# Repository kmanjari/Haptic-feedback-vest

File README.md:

# Haptic Feedback Vest for Obstacle Detection

Visit our instructable at http://www.instructables.com/id/Haptic-Feedback-Vest-for-Obstacle-Detection/ to view a description of the system breakdown!

This design utilizes a stereo camera and software (Python and SimpleCV) that parses the user's surroundings into a depth map using a Raspberry Pi platform. This depth map is then used to vibrate the vest at a particular location to signify an obstacle in that location. For example, a vibration in the upper left region of the vest would indicate a hazard in the upper-body/leftward side of the surroundings. We also developed a PCB and integrated the physical piezoelectric hardware into a vest to create a functional and wearable prototype.

Final project for EE285: Embedded Systems Workshop course at Stanford University.

Contributors: Shalini Ranmuthu, Vikram Prasad, Jacqueline Speiser, Steven Lin, Meredith Burkle

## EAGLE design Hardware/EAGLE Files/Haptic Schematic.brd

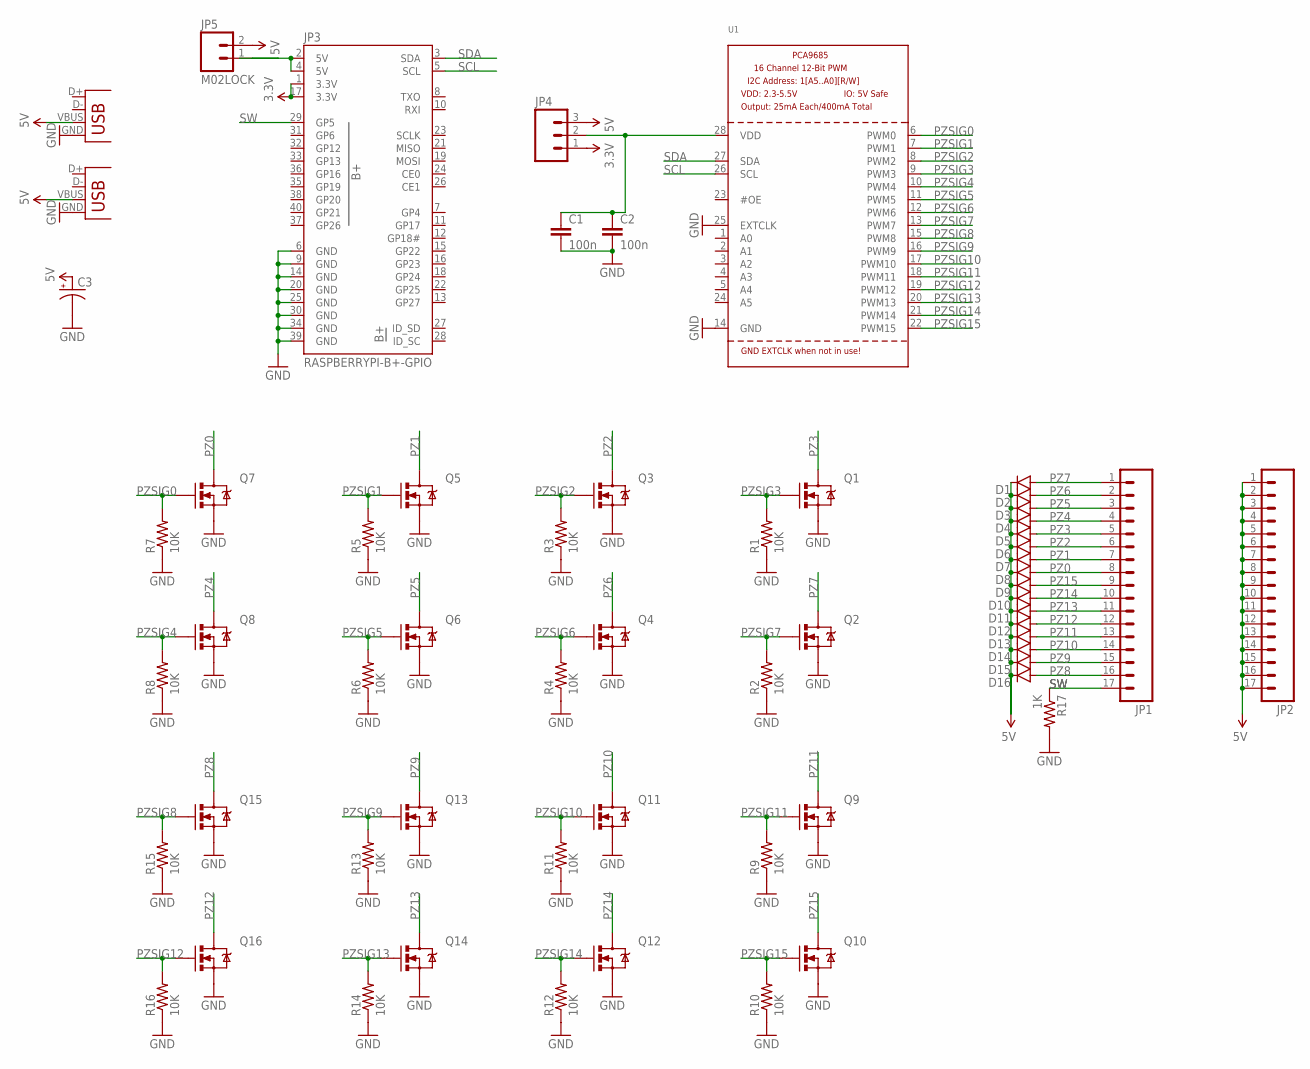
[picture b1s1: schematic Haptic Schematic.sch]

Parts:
C1, C2: 100n; 0805
C3: CAP_POLPTH2; CPOL-RADIAL-10UF-25V
D1, D2, D3, D4, D5, D6, D7, D8, D9, D10, D11, D12, D13, D14, D15, D16: DIODESOD523; SOD523
JP1, JP2: M17; 1X17
JP3: RASPBERRYPI-B+-GPIO; 2X20-SHROUDED
JP4: M03LOCK; 1X03_LOCK
JP5: M02LOCK; 1X02_LOCK
JP6, JP7: USB-B; USB-B-PTH
Q1, Q2, Q3, Q4, Q5, Q6, Q7, Q8, Q9, Q10, Q11, Q12, Q13, Q14, Q15, Q16: MOSFET-NCHANNEL2N7002PW; SOT323
R1, R2, R3, R4, R5, R6, R7, R8, R9, R10, R11, R12, R13, R14, R15, R16: 10K; 0805
R17: 1K; 0805
U1: PCA9685; TSSOP28

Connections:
3.3V: JP3.1 (3.3V), JP3.17 (3.3V), JP4.1
5V: C3.1 (+), D1.C, D2.C, D3.C, D4.C, D5.C, D6.C, D7.C, D8.C, D9.C, D10.C, D11.C, D12.C, D13.C, D14.C, D15.C, D16.C, JP2.1, JP2.2, JP2.3, JP2.4, JP2.5, JP2.6, JP2.7, JP2.8, JP2.9, JP2.10, JP2.11, JP2.12, JP2.13, JP2.14, JP2.15, JP2.16, JP2.17, JP4.3, JP5.2, JP6.VBUS, JP7.VBUS
GND: C1.2, C2.2, C3.2 (-), JP3.6 (GND), JP3.9 (GND), JP3.14 (GND), JP3.20 (GND), JP3.25 (GND), JP3.30 (GND), JP3.34 (GND), JP3.39 (GND), JP6.GND, JP7.GND, Q1.2 (S), Q2.2 (S), Q3.2 (S), Q4.2 (S), Q5.2 (S), Q6.2 (S), Q7.2 (S), Q8.2 (S), Q9.2 (S), Q10.2 (S), Q11.2 (S), Q12.2 (S), Q13.2 (S), Q14.2 (S), Q15.2 (S), Q16.2 (S), R1.1, R2.1, R3.1, R4.1, R5.1, R6.1, R7.1, R8.1, R9.1, R10.1, R11.1, R12.1, R13.1, R14.1, R15.1, R16.1, R17.2, U1.14 (GND), U1.25 (EXTCLK)
unnamed: JP3.2 (5V), JP3.4 (5V), JP5.1
unnamed: C1.1, C2.1, JP4.2, U1.28 (VDD)
PZ0: D8.A, JP1.8, Q7.3 (D)
PZ1: D7.A, JP1.7, Q5.3 (D)
PZ2: D6.A, JP1.6, Q3.3 (D)
PZ3: D5.A, JP1.5, Q1.3 (D)
PZ4: D4.A, JP1.4, Q8.3 (D)
PZ5: D3.A, JP1.3, Q6.3 (D)
PZ6: D2.A, JP1.2, Q4.3 (D)
PZ7: D1.A, JP1.1, Q2.3 (D)
PZ8: D16.A, JP1.16, Q15.3 (D)
PZ9: D15.A, JP1.15, Q13.3 (D)
PZ10: D14.A, JP1.14, Q11.3 (D)
PZ11: D13.A, JP1.13, Q9.3 (D)
PZ12: D12.A, JP1.12, Q16.3 (D)
PZ13: D11.A, JP1.11, Q14.3 (D)
PZ14: D10.A, JP1.10, Q12.3 (D)
PZ15: D9.A, JP1.9, Q10.3 (D)
PZSIG0: Q7.1 (G), R7.2, U1.6 (PWM0)
PZSIG1: Q5.1 (G), R5.2, U1.7 (PWM1)
PZSIG2: Q3.1 (G), R3.2, U1.8 (PWM2)
PZSIG3: Q1.1 (G), R1.2, U1.9 (PWM3)
PZSIG4: Q8.1 (G), R8.2, U1.10 (PWM4)
PZSIG5: Q6.1 (G), R6.2, U1.11 (PWM5)
PZSIG6: Q4.1 (G), R4.2, U1.12 (PWM6)
PZSIG7: Q2.1 (G), R2.2, U1.13 (PWM7)
PZSIG8: Q15.1 (G), R15.2, U1.15 (PWM8)
PZSIG9: Q13.1 (G), R13.2, U1.16 (PWM9)
PZSIG10: Q11.1 (G), R11.2, U1.17 (PWM10)
PZSIG11: Q9.1 (G), R9.2, U1.18 (PWM11)
PZSIG12: Q16.1 (G), R16.2, U1.19 (PWM12)
PZSIG13: Q14.1 (G), R14.2, U1.20 (PWM13)
PZSIG14: Q12.1 (G), R12.2, U1.21 (PWM14)
PZSIG15: Q10.1 (G), R10.2, U1.22 (PWM15)
SCL: JP3.5 (SCL), U1.26 (SCL)
SDA: JP3.3 (SDA), U1.27 (SDA)
SW: JP1.17, JP3.29 (GP5), R17.1

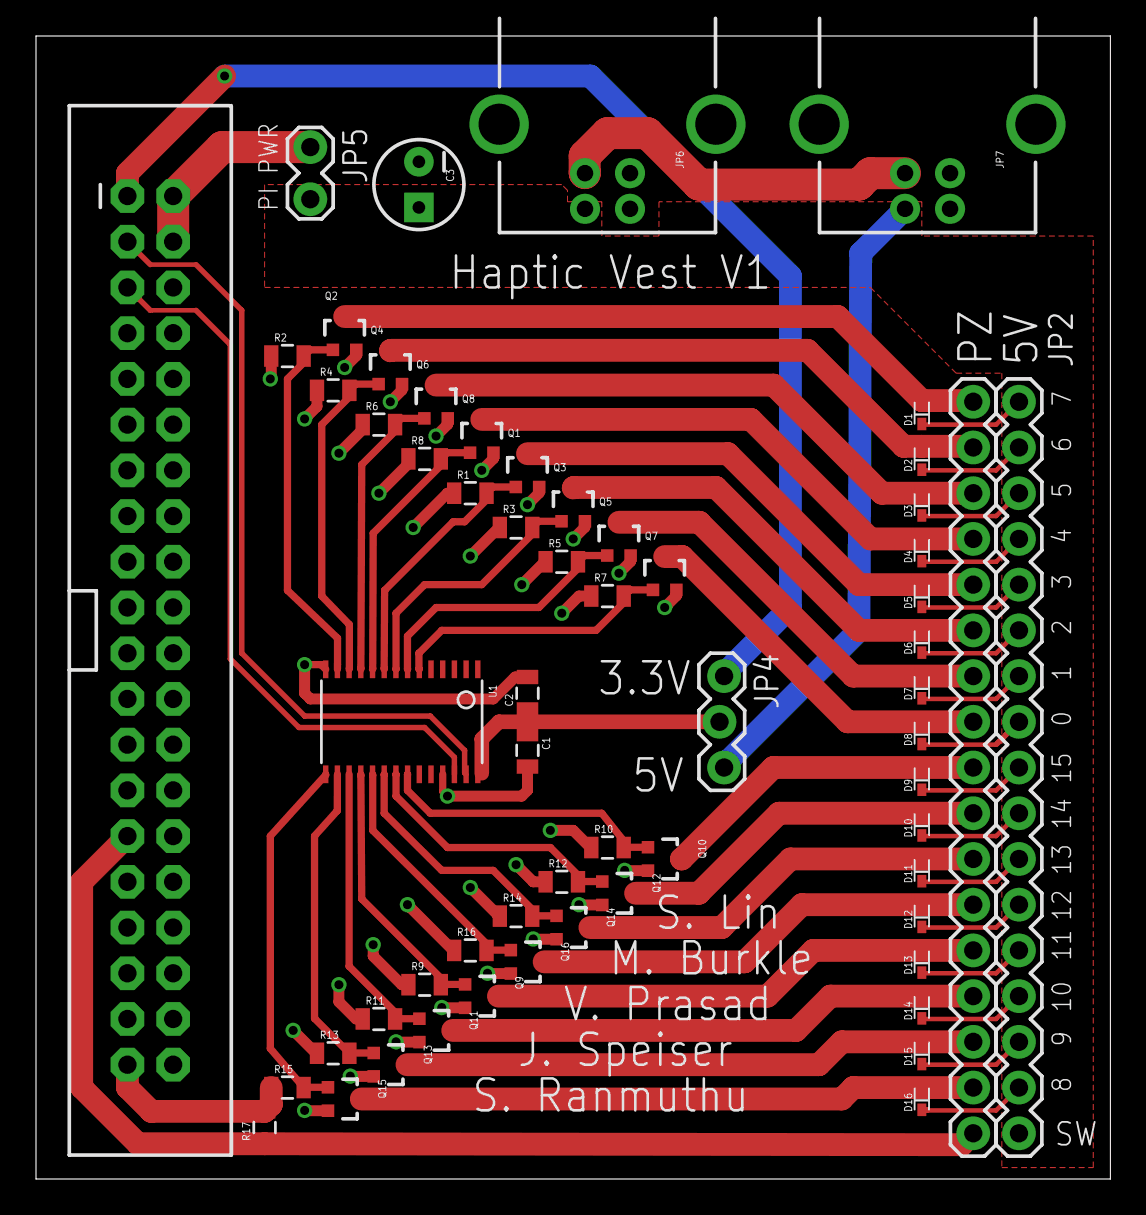
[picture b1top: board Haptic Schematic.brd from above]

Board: 2 copper layers, 59.7 x 63.5 mm, 60 parts (0 on the bottom side), 40 nets.

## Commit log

2018-04-02 project contents

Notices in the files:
parts and their libraries:
SparkFun-DiscreteSemi: Licensing: Creative Commons ShareAlike 4.0 International - https://creativecommons.org/licenses/by-sa/4.0
SparkFun-Resistors: Licensing: CC v3.0 Share-Alike You are welcome to use this library for commercial purposes.
